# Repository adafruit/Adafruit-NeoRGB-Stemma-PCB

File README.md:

## Adafruit NeoRGB Stemma - NeoPixel to RGB PWM LEDs and Strips - STEMMA JST PH 2mm PCB

<a href="http://www.adafruit.com/products/5888"><br/>
Click here to purchase one from the Adafruit shop</a>

PCB files for the Adafruit NeoRGB Stemma - NeoPixel to RGB PWM LEDs and Strips - STEMMA JST PH 2mm. 

Format is EagleCAD schematic and board layout
* https://www.adafruit.com/product/5888

### Description

Whenever we're working with 'true analog' LED strips, that have 1-3 channels of RGB or White LEDs, we wish we had already invented to make wiring them easier: controlling these strips takes a bit of wiring since they almost always need 12VDC and driver FETs. Now, we've finally created the Adafruit NeoRGB Stemma board - which will make our lives easier, and maybe even some customer's too!

The NeoRGB is a no-soldering, plug-and-play STEMMA board with a 2mm JST PH connector on one end, and a 5-pin 0.1" screw terminal block on the other. It can convert standard 800KHz NeoPixel signal using a WS2811F chip to AO3406 N-channel FETs that are high efficiency and can sink a chunk of current - 3 Amps a piece with 50milliOhm Ron!

Basically, this means that you can treat any PWM-able common-anode RGB LED strip or LED as a single NeoPixel, at up to 16V and 3 Amps per channel. Perfect for large analog LEDs or arrays, LED strips, even ones that are not RGB, such as controlling 3 independent single-channel LEDs or strips. Note that the WS2811 bare chips don't support 4 channels, so this won't work on RGBW strips.

Usage is easy. First you'll need a 2mm JST PH cable, such as this one with pins. Then pick one of two powering options

If you are using less than 2A of current total across all 3 channels:

	1. Connect the white wire to your NeoPixel-compatible signal, 3 or 5V logic.
	2. Connect the red wire to 3-16VDC, this will power the LED strip
	3. Connect the black ground wire to your microcontroller and power supply shared ground
	
If you are using more than 2A of current total across all 3 channels, you'll need to wire the power supply to the terminal block since JST PH connectors are only rated for 2A.

	1. Connect the white wire to your NeoPixel-compatible signal, 3 or 5V logic.
	2. Connect your 3-16V power supply positive pin to the V+ to the terminal block, keep the red wire from being used by taping it or cutting it off.
	3. Connect the 3-16V power supply ground pin to the GND on the terminal block
	4. Connect the black wire as a 'reference' ground to your microcontroller that is providing the NeoPixel signal

An onboard green ON LED will let you know that it is powered correctly, and a red Signal LED will lightly blink when data is sent on the Signal line. If you need to chain more than one, or want to connect some other NeoPixels to the output, there's a pin for the Output signal on the board.

<b>Revision History:</b>

* As of February 13, 2025 - We've updated this design to add a built-in level shifter so it will work flawlessly with 3V or 5V NeoPixel signals.

### License

Adafruit invests time and resources providing this open source design, please support Adafruit and open-source hardware by purchasing products from [Adafruit](https://www.adafruit.com)!

Designed by Limor Fried/Ladyada for Adafruit Industries.

Creative Commons Attribution/Share-Alike, all text above must be included in any redistribution. 
See license.txt for additional details.

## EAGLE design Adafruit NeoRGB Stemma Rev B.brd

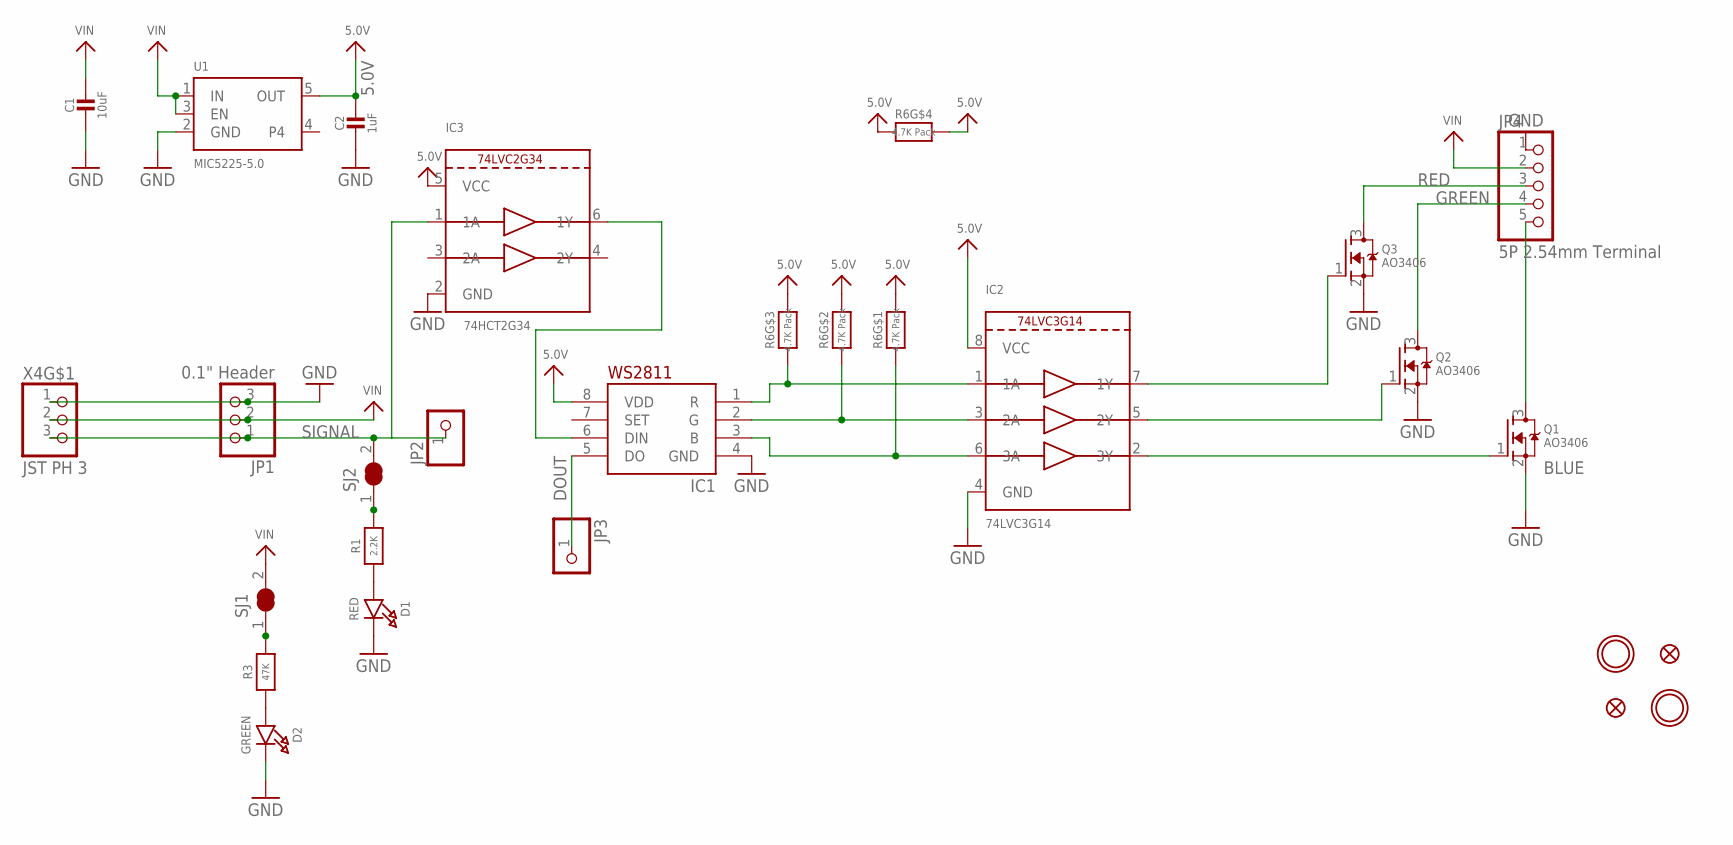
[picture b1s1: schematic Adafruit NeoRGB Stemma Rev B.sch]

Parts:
C1: 10uF; 0805-NO
C2: 1uF; 0603-NO
D1: RED; CHIPLED_0603_NOOUTLINE
D2: GREEN; CHIPLED_0603_NOOUTLINE
FID2, FID3: FIDUCIAL_1MM
IC1: WS2811F; FSOP-8
IC2: 74LVC3G14; VFSOP-8
IC3: 74HCT2G34; SC70-6L
JP1: 0.1" Header; 1X03_OVAL
JP2, JP3: HEADER-1X1ROUND; 1X01_ROUND
JP4: 5P 2.54mm Terminal; 1X05_2.54MMTERMINAL
Q1, Q2, Q3: AO3406; SOT23-WIDE
R1: 2.2K; 0603-NO
R3: 47K; 0603-NO
R6: 4.7K Pack; RESPACK_4X0402
SJ1, SJ2: SOLDERJUMPER_CLOSED; SOLDERJUMPER_CLOSEDWIRE
U1: MIC5225-5.0; SOT23-5; JLC_ROTATION 0
U$1, U$8: MOUNTINGHOLE2.5; MOUNTINGHOLE_2.5_PLATED
X4: JST PH 3; JSTPH3

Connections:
5.0V: C2.1, IC1.8 (VDD), IC2.8 (VCC), IC3.5 (VCC), R6.4 (1), R6.5 (2), R6.6 (2), R6.7 (2), R6.8 (2), U1.5 (OUT)
BLUE: JP4.5, Q1.3 (D)
DOUT: IC1.5 (DO), JP3.1
GND: C1.2, C2.2, D1.C, D2.C, IC1.4 (GND), IC2.4 (GND), IC3.2 (GND), JP1.3, JP4.1, Q1.2 (S), Q2.2 (S), Q3.2 (S), U1.2 (GND), X4.1
GREEN: JP4.4, Q2.3 (D)
unnamed: R3.2, SJ1.1
unnamed: D1.A, R1.1
unnamed: R1.2, SJ2.1
unnamed: IC2.2 (3Y), Q1.1 (G)
unnamed: IC2.5 (2Y), Q2.1 (G)
unnamed: IC2.7 (1Y), Q3.1 (G)
unnamed: IC1.1 (R), IC2.1 (1A), R6.3 (1)
unnamed: IC1.2 (G), IC2.3 (2A), R6.2 (1)
unnamed: IC1.3 (B), IC2.6 (3A), R6.1
unnamed: IC1.6 (DIN), IC3.6 (1Y)
unnamed: D2.A, R3.1
RED: JP4.3, Q3.3 (D)
SIGNAL: IC3.1 (1A), JP1.1, JP2.1, SJ2.2, X4.3
VIN: C1.1, JP1.2, JP4.2, SJ1.2, U1.1 (IN), U1.3 (EN), X4.2

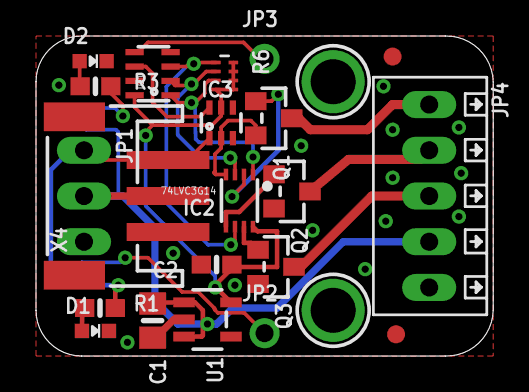
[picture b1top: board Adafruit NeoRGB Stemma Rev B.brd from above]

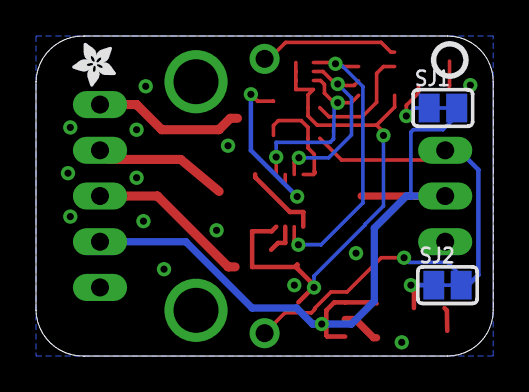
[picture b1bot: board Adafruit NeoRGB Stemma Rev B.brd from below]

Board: 2 copper layers, 25.4 x 17.8 mm, 46 parts (16 on the bottom side), 19 nets.

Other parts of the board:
E$1: ADAFRUIT_2.5MM
PLABEL0: PLABEL0
PLABEL1: PLABEL1
PLABEL2: PLABEL2
PLABEL3: PLABEL3
PLABEL4: PLABEL4
PLABEL5: PLABEL5
PLABEL6: PLABEL6
PLABEL7: PLABEL7
PLABEL8: PLABEL8
PLABEL9: PLABEL9
PLABEL10: PLABEL10
PLABEL11: PLABEL11
PLABEL12: PLABEL12
PLABEL13: PLABEL13
PLABEL14: PLABEL14
PLABEL15: PLABEL15
PLABEL16: PLABEL16
PLABEL17: PLABEL17
PLABEL18: PLABEL18
U$5: PCBFEAT-REV-040

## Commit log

2024-02-14 cookiecutter
2024-02-14 fix image
2025-02-20 adding rev B
2025-02-20 rev a label

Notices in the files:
parts and their libraries:
microbuilder: This work is placed in the public domain, and may be freely used for commercial and non-commercial work with the following conditions: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
